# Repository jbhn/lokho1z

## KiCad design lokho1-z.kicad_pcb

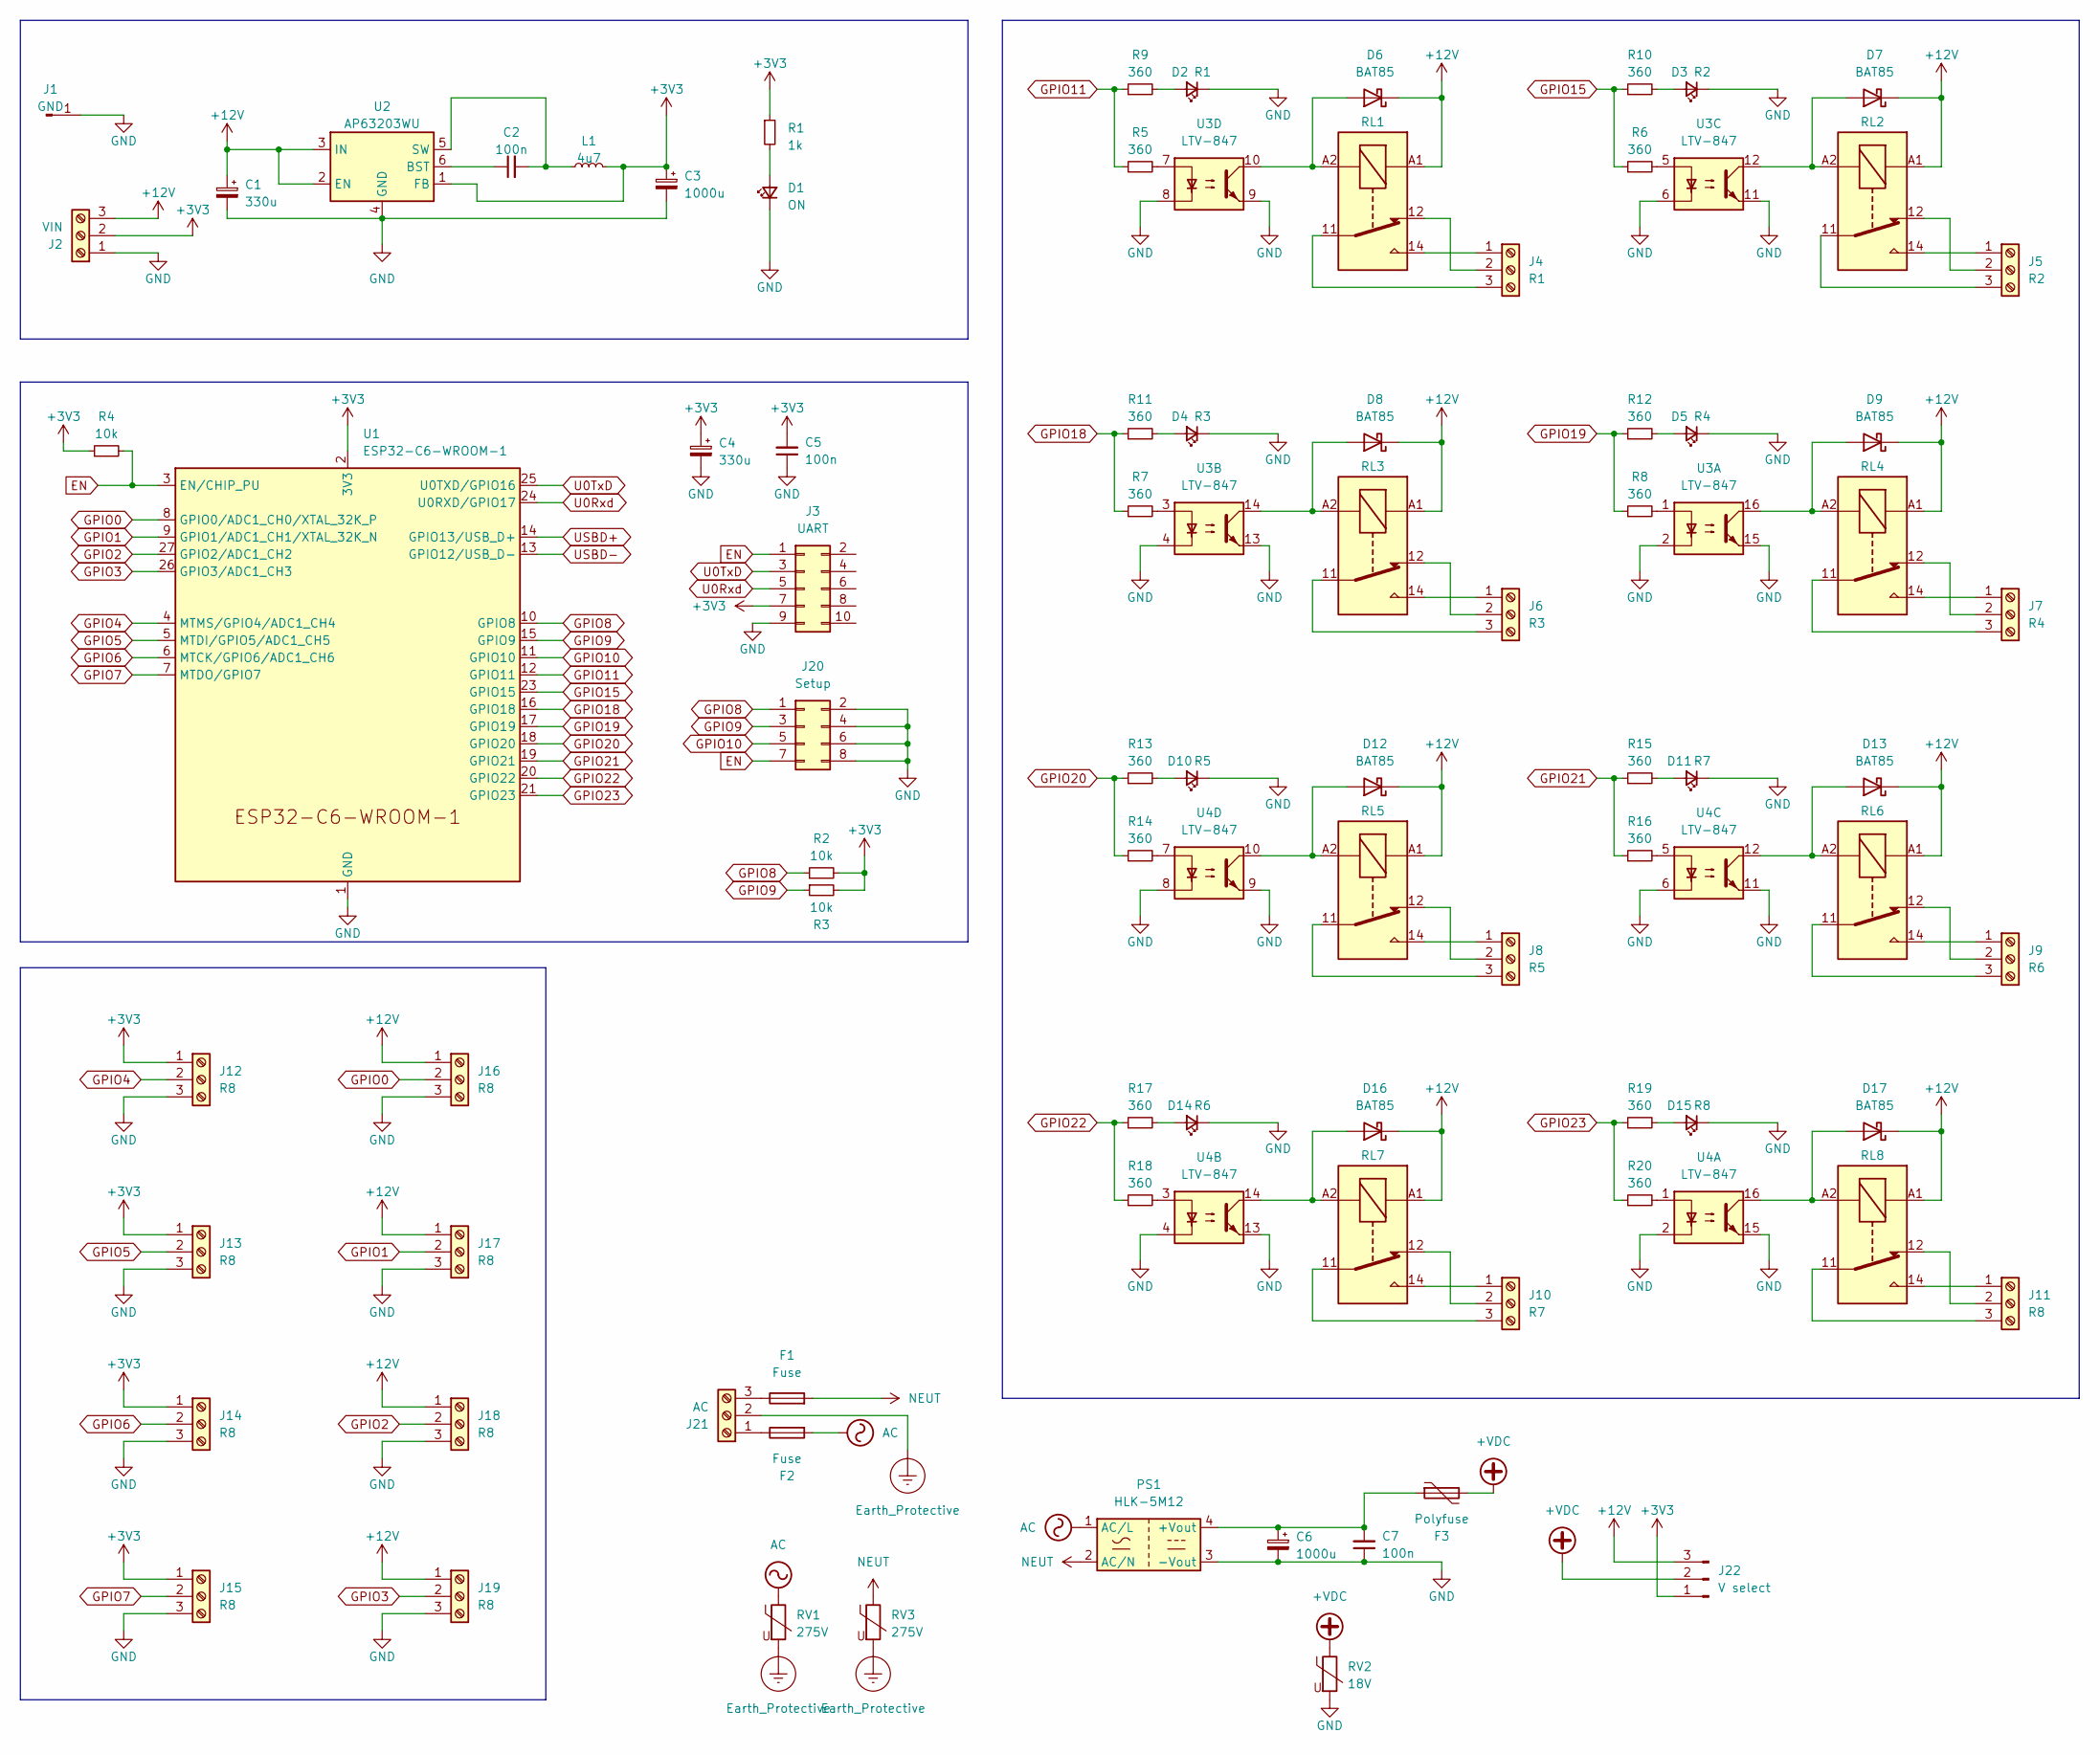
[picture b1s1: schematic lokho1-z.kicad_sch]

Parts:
C1, C4: 330u; CP_Radial_D8.0mm_P3.50mm
C2, C5, C7: 100n; C_Disc_D5.0mm_W2.5mm_P5.00mm
C3, C6: 1000u; CP_Radial_D8.0mm_P3.50mm
D1: ON; LED_D3.0mm
D2: R1; LED_D3.0mm
D3: R2; LED_D3.0mm
D4: R3; LED_D3.0mm
D5: R4; LED_D3.0mm
D6, D7, D8, D9, D12, D13, D16, D17: BAT85; D_DO-35_SOD27_P7.62mm_Horizontal
D10: R5; LED_D3.0mm
D11: R7; LED_D3.0mm
D14: R6; LED_D3.0mm
D15: R8; LED_D3.0mm
F1, F2: Fuse; Fuseholder_Cylinder-5x20mm_EATON_HBV_Vertical_Closed
F3: Polyfuse; C_Disc_D8.0mm_W2.5mm_P5.00mm
J1: GND; Pin_D1.0mm_L10.0mm
J2: VIN; TerminalBlock_4Ucon_1x03_P3.50mm_Horizontal
J3: UART; PinHeader_2x05_P2.54mm_Vertical
J4: R1; TerminalBlock_4Ucon_1x03_P3.50mm_Horizontal
J5: R2; TerminalBlock_4Ucon_1x03_P3.50mm_Horizontal
J6: R3; TerminalBlock_4Ucon_1x03_P3.50mm_Horizontal
J7: R4; TerminalBlock_4Ucon_1x03_P3.50mm_Horizontal
J8: R5; TerminalBlock_4Ucon_1x03_P3.50mm_Horizontal
J9: R6; TerminalBlock_4Ucon_1x03_P3.50mm_Horizontal
J10: R7; TerminalBlock_4Ucon_1x03_P3.50mm_Horizontal
J11, J12, J13, J14, J15, J16, J17, J18, J19: R8; TerminalBlock_4Ucon_1x03_P3.50mm_Horizontal
J20: Setup; PinHeader_2x04_P2.54mm_Vertical
J21: AC; TerminalBlock_4Ucon_1x03_P3.50mm_Horizontal
J22: V select; PinHeader_1x03_P2.54mm_Vertical
L1: 4u7; L_Radial_D7.5mm_P3.50mm_Fastron_07P
PS1: HLK-5M12; Converter_ACDC_Hi-Link_HLK-5Mxx
R1: 1k; R_Axial_DIN0204_L3.6mm_D1.6mm_P2.54mm_Vertical
R2, R3, R4: 10k; R_Axial_DIN0204_L3.6mm_D1.6mm_P2.54mm_Vertical
R5, R6, R7, R8, R9, R10, R11, R12, R13, R14, R15, R16, R17, R18, R19, R20: 360; R_Axial_DIN0204_L3.6mm_D1.6mm_P2.54mm_Vertical
RL1, RL2, RL3, RL4, RL5, RL6, RL7, RL8: RM87N
RV1, RV3: 275V; RV_Disc_D21.5mm_W4.3mm_P10mm
RV2: 18V; RV_Disc_D7mm_W3.4mm_P5mm
U1: ESP32-C6-WROOM-1
U2: AP63203WU; TSOT-23-6
U3, U4: LTV-847; DIP-16_W7.62mm

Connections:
+3V3: C3.1, C4.1, C5.2, J2.2, J3.7, J12.1, J13.1, J14.1, J15.1, J22.1, L1.2, R1.1, R2.2, R3.2, R4.1, U1.2 (3V3), U2.1 (FB)
+12V: C1.1, D6.1 (K), D7.1 (K), D8.1 (K), D9.1 (K), D12.1 (K), D13.1 (K), D16.1 (K), D17.1 (K), J2.3, J16.1, J17.1, J18.1, J19.1, J22.3, RL1.A1, RL2.A1, RL3.A1, RL4.A1, RL5.A1, RL6.A1, RL7.A1, RL8.A1, U2.2 (EN), U2.3 (IN)
+VDC: F3.2, J22.2, RV2.1
AC: F2.2, PS1.1 (AC/L), RV1.1
EN: J3.1, J20.7, R4.2, U1.3 (EN/CHIP_PU)
Earth_Protective: J21.2, RV1.2, RV3.2
GND: C1.2, C3.2, C4.2, C5.1, C6.2, C7.1, D1.1 (K), D2.1 (K), D3.1 (K), D4.1 (K), D5.1 (K), D10.1 (K), D11.1 (K), D14.1 (K), D15.1 (K), J1.1, J2.1, J3.9, J12.3, J13.3, J14.3, J15.3, J16.3, J17.3, J18.3, J19.3, J20.2, J20.4, J20.6, J20.8, PS1.3 (-Vout), RV2.2, U1.1 (GND), U1.28 (GND), U1.29 (GND), U2.4 (GND), U3.2, U3.4, U3.6, U3.8, U3.9, U3.11, U3.13, U3.15, U4.2, U4.4, U4.6, U4.8, U4.9, U4.11, U4.13, U4.15
GPIO0: J16.2, U1.8 (GPIO0/ADC1_CH0/XTAL_32K_P)
GPIO1: J17.2, U1.9 (GPIO1/ADC1_CH1/XTAL_32K_N)
GPIO2: J18.2, U1.27 (GPIO2/ADC1_CH2)
GPIO3: J19.2, U1.26 (GPIO3/ADC1_CH3)
GPIO4: J12.2, U1.4 (MTMS/GPIO4/ADC1_CH4)
GPIO5: J13.2, U1.5 (MTDI/GPIO5/ADC1_CH5)
GPIO6: J14.2, U1.6 (MTCK/GPIO6/ADC1_CH6)
GPIO7: J15.2, U1.7 (MTDO/GPIO7)
GPIO8: J20.1, R2.1, U1.10 (GPIO8)
GPIO9: J20.3, R3.1, U1.15 (GPIO9)
GPIO10: J20.5, U1.11 (GPIO10)
GPIO11: R5.1, R9.1, U1.12 (GPIO11)
GPIO15: R6.1, R10.1, U1.23 (GPIO15)
GPIO18: R7.1, R11.1, U1.16 (GPIO18)
GPIO19: R8.1, R12.1, U1.17 (GPIO19)
GPIO20: R13.1, R14.1, U1.18 (GPIO20)
GPIO21: R15.1, R16.1, U1.19 (GPIO21)
GPIO22: R17.1, R18.1, U1.20 (GPIO22)
GPIO23: R19.1, R20.1, U1.21 (GPIO23)
NEUT: F1.2, PS1.2 (AC/N), RV3.1
unnamed: D1.2 (A), R1.2
unnamed: D2.2 (A), R9.2
unnamed: D3.2 (A), R10.2
unnamed: D4.2 (A), R11.2
unnamed: D5.2 (A), R12.2
unnamed: D6.2 (A), RL1.A2, U3.10
unnamed: D7.2 (A), RL2.A2, U3.12
unnamed: D8.2 (A), RL3.A2, U3.14
unnamed: D9.2 (A), RL4.A2, U3.16
unnamed: D10.2 (A), R13.2
unnamed: D11.2 (A), R15.2
unnamed: D12.2 (A), RL5.A2, U4.10
unnamed: D13.2 (A), RL6.A2, U4.12
unnamed: D14.2 (A), R17.2
unnamed: D15.2 (A), R19.2
unnamed: D16.2 (A), RL7.A2, U4.14
unnamed: D17.2 (A), RL8.A2, U4.16
unnamed: J4.1, RL1.14
unnamed: J4.2, RL1.12
unnamed: J4.3, RL1.11
unnamed: J5.1, RL2.14
unnamed: J5.2, RL2.12
unnamed: J5.3, RL2.11
unnamed: J6.1, RL3.14
unnamed: J6.2, RL3.12
unnamed: J6.3, RL3.11
unnamed: J7.1, RL4.14
unnamed: J7.2, RL4.12
unnamed: J7.3, RL4.11
unnamed: J8.1, RL5.14
unnamed: J8.2, RL5.12
unnamed: J8.3, RL5.11
unnamed: J9.1, RL6.14
unnamed: J9.2, RL6.12
unnamed: J9.3, RL6.11
unnamed: J10.1, RL7.14
unnamed: J10.2, RL7.12
unnamed: J10.3, RL7.11
unnamed: J11.1, RL8.14
unnamed: J11.2, RL8.12
unnamed: J11.3, RL8.11
unnamed: F2.1, J21.1
unnamed: F1.1, J21.3
unnamed: C6.1, C7.2, F3.1, PS1.4 (+Vout)
unnamed: R5.2, U3.7
unnamed: R6.2, U3.5
unnamed: R7.2, U3.3
unnamed: R8.2, U3.1
unnamed: R14.2, U4.7
unnamed: R16.2, U4.5
unnamed: R18.2, U4.3
unnamed: R20.2, U4.1
unnamed: C2.1, U2.6 (BST)
unnamed: C2.2, L1.1, U2.5 (SW)
U0Rxd: J3.5, U1.24 (U0RXD/GPIO17)
U0TxD: J3.3, U1.25 (U0TXD/GPIO16)
USBD+: U1.14 (GPIO13/USB_D+)
USBD-: U1.13 (GPIO12/USB_D-)

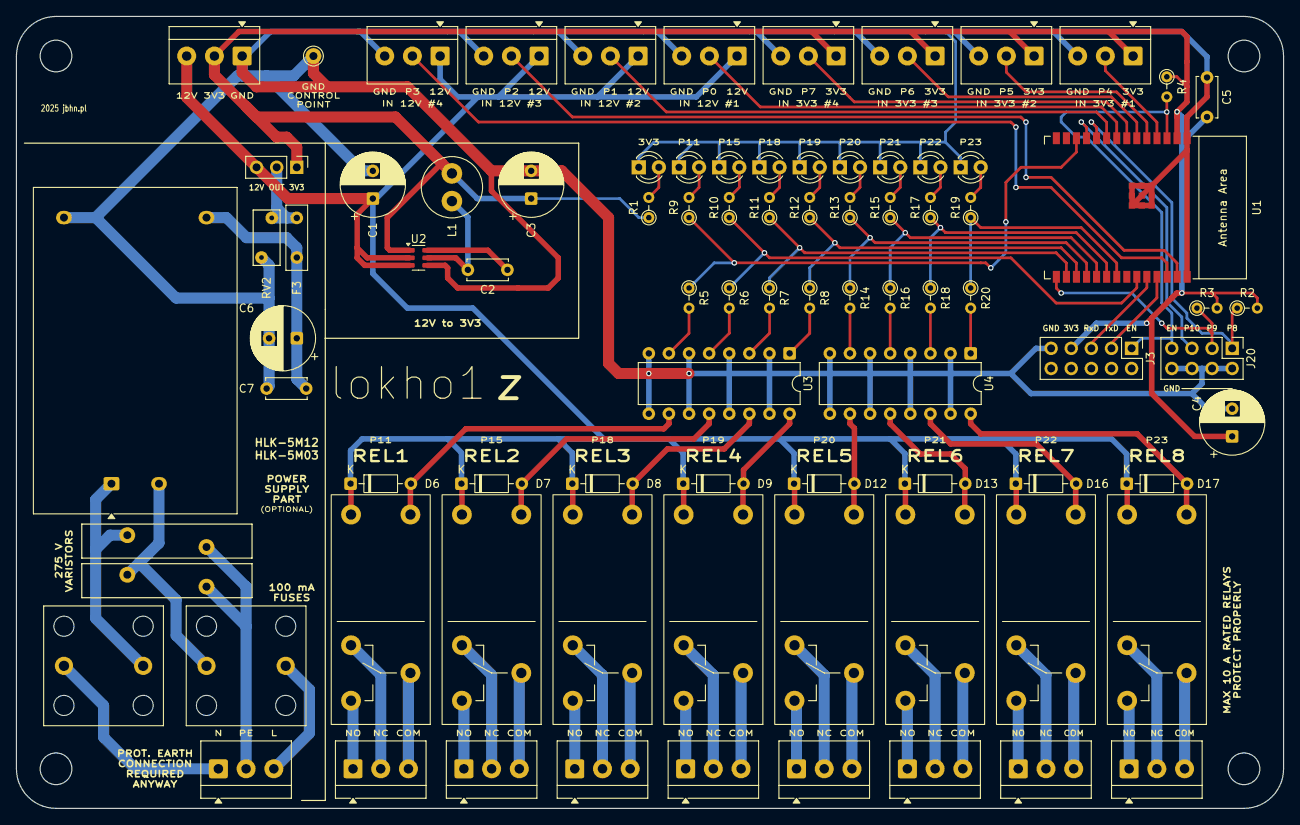
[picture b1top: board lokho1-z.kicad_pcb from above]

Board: 2 copper layers, 160.0 x 100.0 mm, 86 parts (0 on the bottom side), 83 nets.

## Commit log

2026-02-01 initial public commit
2026-02-01 license
